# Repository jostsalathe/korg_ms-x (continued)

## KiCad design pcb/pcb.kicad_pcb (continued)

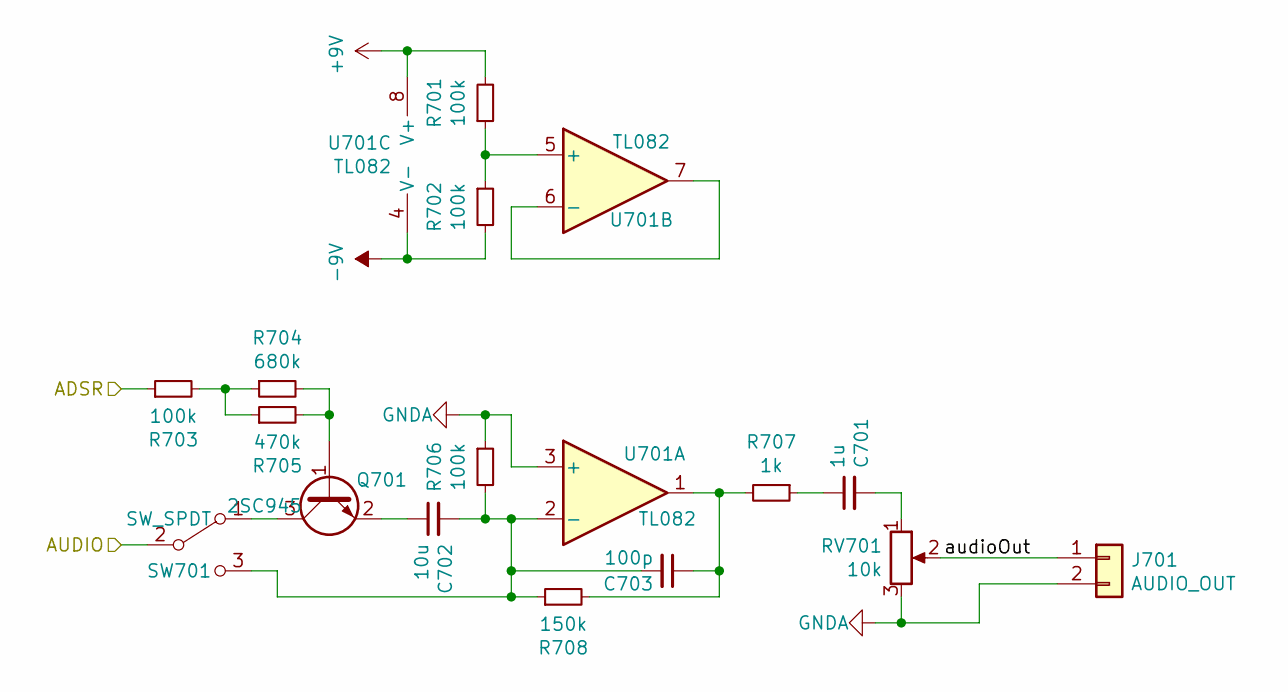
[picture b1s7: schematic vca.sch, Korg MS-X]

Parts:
C701: 1u; C_0805_2012Metric_Pad1.18x1.45mm_HandSolder; LCSC C28323
C702: 10u; C_0805_2012Metric_Pad1.18x1.45mm_HandSolder; LCSC C15850
C703: 100p; C_0805_2012Metric_Pad1.18x1.45mm_HandSolder; LCSC C1790
J701: AUDIO_OUT; PinHeader_1x02_P2.54mm_Vertical
Q701: 2SC945; SOT-23; LCSC C181154
R701, R702, R703, R706: 100k; R_0805_2012Metric_Pad1.20x1.40mm_HandSolder; LCSC C149504
R704: 680k; R_0805_2012Metric_Pad1.20x1.40mm_HandSolder; LCSC C17797
R705: 470k; R_0805_2012Metric_Pad1.20x1.40mm_HandSolder; LCSC C17709
R707: 1k; R_0805_2012Metric_Pad1.20x1.40mm_HandSolder; LCSC C17513
R708: 150k; R_0805_2012Metric_Pad1.20x1.40mm_HandSolder; LCSC C17470
RV701: 10k; PinHeader_1x03_P2.54mm_Vertical
SW701: SW_SPDT; PinHeader_1x03_P2.54mm_Vertical
U701: TL082; SOIC-8_3.9x4.9mm_P1.27mm; LCSC C9385

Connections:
+9V: R701.2, U701.8 (V+); also elsewhere on the board
-9V: R702.2, U701.4 (V-); also elsewhere on the board
/ADSR: R703.1; also elsewhere on the board
/AUDIO_RESONANCE: SW701.2 (B); also elsewhere on the board
/vca/audioOut: J701.1, RV701.2
GNDA: J701.2, R706.1, RV701.3, U701.3 (+); also elsewhere on the board
unnamed: C701.1, R707.1
unnamed: C701.2, RV701.1
unnamed: C702.1, Q701.2 (E)
unnamed: C702.2, C703.2, R706.2, R708.1, SW701.3 (C), U701.2 (-)
unnamed: C703.1, R707.2, R708.2, U701.1
unnamed: Q701.1 (B), R704.2, R705.2
unnamed: Q701.3 (C), SW701.1 (A)
unnamed: R701.1, R702.1, U701.5 (+)
unnamed: R703.2, R704.1, R705.1
unnamed: U701.6 (-), U701.7

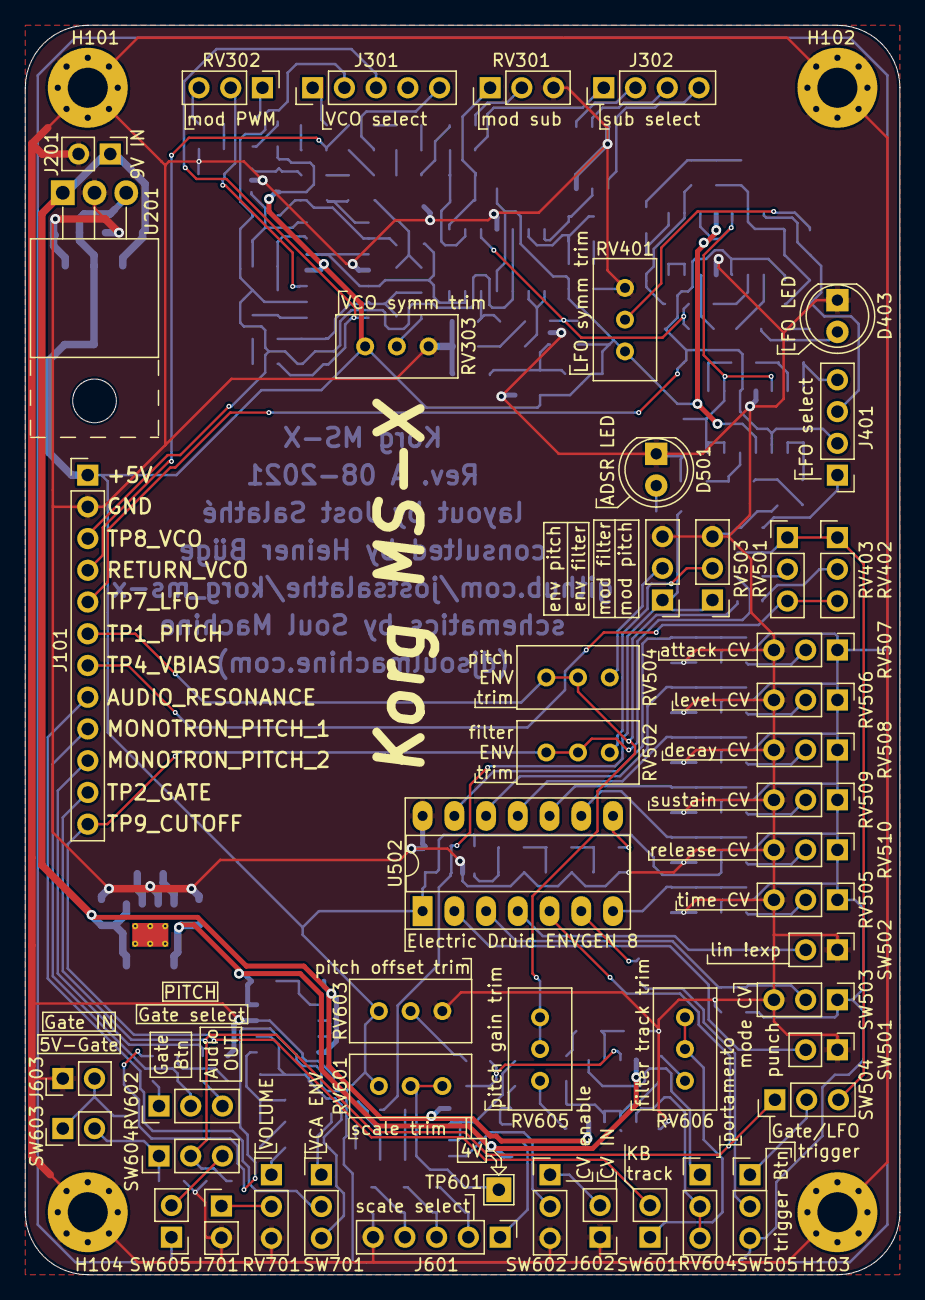
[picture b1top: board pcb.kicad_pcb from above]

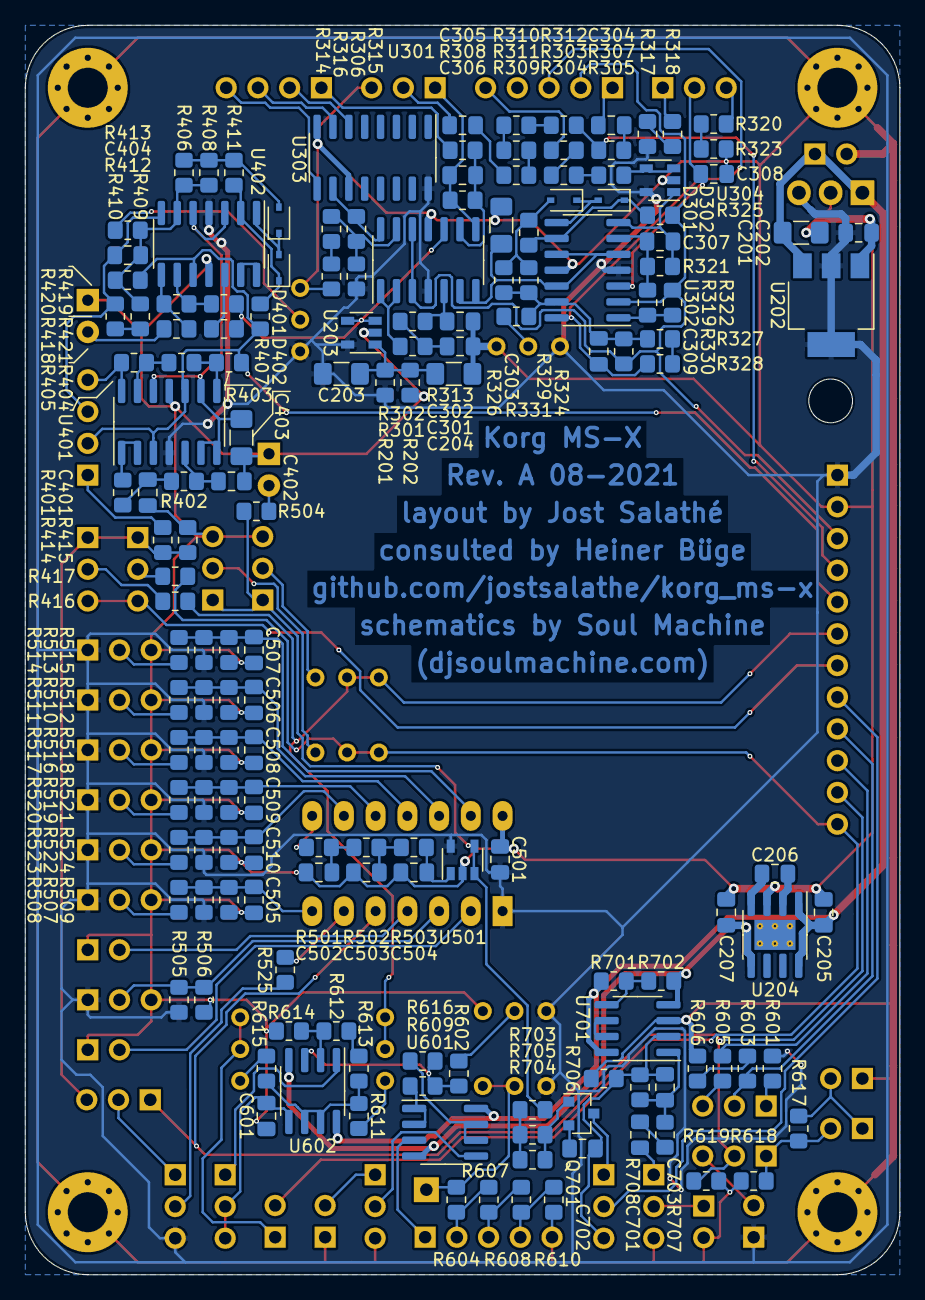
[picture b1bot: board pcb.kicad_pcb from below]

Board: 2 copper layers, 70.0 x 100.0 mm, 211 parts (159 on the bottom side), 143 nets.

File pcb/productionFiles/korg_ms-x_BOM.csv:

Comment,Designator,Footprint,LCSC Part Number
"100u","C201,C303,C403","Capacitor_SMD:C_1206_3216Metric_Pad1.42x1.75mm_HandSolder","C312983"
"10u","C202,C205,C206,C207,C308,C401,C402,C506,C601,C702","Capacitor_SMD:C_0805_2012Metric_Pad1.18x1.45mm_HandSolder","C15850"
"47u","C203,C204","Capacitor_SMD:C_1206_3216Metric_Pad1.42x1.75mm_HandSolder","C96123"
"1u","C301,C302,C304,C305,C701","Capacitor_SMD:C_0805_2012Metric_Pad1.18x1.45mm_HandSolder","C28323"
"100n","C306,C501,C505,C507,C508,C509,C510","Capacitor_SMD:C_0805_2012Metric_Pad1.18x1.45mm_HandSolder","C49678"
"470n","C307","Capacitor_SMD:C_0805_2012Metric_Pad1.18x1.45mm_HandSolder","C13967"
"22p","C309","Capacitor_SMD:C_0805_2012Metric_Pad1.18x1.45mm_HandSolder","C1804"
"500p","C404","Capacitor_SMD:C_0805_2012Metric_Pad1.18x1.45mm_HandSolder","C1747"
"47n","C502","Capacitor_SMD:C_0805_2012Metric_Pad1.18x1.45mm_HandSolder","C53134"
"4n7","C503","Capacitor_SMD:C_0805_2012Metric_Pad1.18x1.45mm_HandSolder","C1744"
"470p","C504","Capacitor_SMD:C_0805_2012Metric_Pad1.18x1.45mm_HandSolder","C1743"
"100p","C703","Capacitor_SMD:C_0805_2012Metric_Pad1.18x1.45mm_HandSolder","C1790"
"1N4148WS","D301,D302,D401,D402","Diode_SMD:D_SOD-323","C2128"
"LED","D403,D501","LED_THT:LED_D5.0mm",""
"MountingHole_Pad","H101,H102,H103,H104","MountingHole:MountingHole_3.2mm_M3_Pad_Via",""
"MONOTRON","J101","Connector_PinHeader_2.54mm:PinHeader_1x12_P2.54mm_Vertical",""
"PWR_IN","J201","Connector_PinHeader_2.54mm:PinHeader_1x02_P2.54mm_Vertical",""
"VCO_SEL","J301","Connector_PinHeader_2.54mm:PinHeader_1x05_P2.54mm_Vertical",""
"SUB_SEL","J302","Connector_PinHeader_2.54mm:PinHeader_1x04_P2.54mm_Vertical",""
"LFO_SEL","J401","Connector_PinHeader_2.54mm:PinHeader_1x04_P2.54mm_Vertical",""
"SCALE_SEL","J601","Connector_PinHeader_2.54mm:PinHeader_1x05_P2.54mm_Vertical",""
"CV_IN","J602","Connector_PinHeader_2.54mm:PinHeader_1x02_P2.54mm_Vertical",""
"GATE_IN","J603","Connector_PinHeader_2.54mm:PinHeader_1x02_P2.54mm_Vertical",""
"AUDIO_OUT","J701","Connector_PinHeader_2.54mm:PinHeader_1x02_P2.54mm_Vertical",""
"Net-Tie_2","NT201","NetTie:NetTie-2_SMD_Pad0.5mm",""
"2SC945","Q701","Package_TO_SOT_SMD:SOT-23","C181154"
"10k","R201,R202,R417,R501,R505,R506,R507,R509,R510,R512,R513,R515,R516,R518,R519,R521,R522,R524,R604,R607,R608,R610","Resistor_SMD:R_0805_2012Metric_Pad1.20x1.40mm_HandSolder","C17414"
"100k","R301,R302,R303,R304,R305,R307,R309,R310,R311,R312,R318,R324,R325,R326,R327,R328,R329,R330,R331,R401,R402,R404,R406,R407,R408,R409,R410,R411,R412,R413,R420,R421,R502,R602,R609,R612,R613,R614,R616,R701,R702,R703,R706","Resistor_SMD:R_0805_2012Metric_Pad1.20x1.40mm_HandSolder","C149504"
"33k","R306","Resistor_SMD:R_0805_2012Metric_Pad1.20x1.40mm_HandSolder","C17633"
"47","R308","Resistor_SMD:R_0805_2012Metric_Pad1.20x1.40mm_HandSolder","C17714"
"5k6","R313,R321","Resistor_SMD:R_0805_2012Metric_Pad1.20x1.40mm_HandSolder","C4382"
"4k7","R314","Resistor_SMD:R_0805_2012Metric_Pad1.20x1.40mm_HandSolder","C17673"
"1M","R315,R322,R403,R503","Resistor_SMD:R_0805_2012Metric_Pad1.20x1.40mm_HandSolder","C17514"
"47k","R316,R618","Resistor_SMD:R_0805_2012Metric_Pad1.20x1.40mm_HandSolder","C17713"
"56k","R317","Resistor_SMD:R_0805_2012Metric_Pad1.20x1.40mm_HandSolder","C17756"
"12","R319","Resistor_SMD:R_0805_2012Metric_Pad1.20x1.40mm_HandSolder","C204200"
"39k","R320,R419","Resistor_SMD:R_0805_2012Metric_Pad1.20x1.40mm_HandSolder","C25826"
"220k","R323","Resistor_SMD:R_0805_2012Metric_Pad1.20x1.40mm_HandSolder","C17556"
"22k","R405","Resistor_SMD:R_0805_2012Metric_Pad1.20x1.40mm_HandSolder","C17560"
"2k2","R414,R415,R416","Resistor_SMD:R_0805_2012Metric_Pad1.20x1.40mm_HandSolder","C17520"
"180","R418,R504","Resistor_SMD:R_0805_2012Metric_Pad1.20x1.40mm_HandSolder","C25270"
"1k","R508,R511,R514,R517,R520,R523,R525,R601,R605,R619,R707","Resistor_SMD:R_0805_2012Metric_Pad1.20x1.40mm_HandSolder","C17513"
"56","R603","Resistor_SMD:R_0805_2012Metric_Pad1.20x1.40mm_HandSolder","C17757"
"390","R606","Resistor_SMD:R_0805_2012Metric_Pad1.20x1.40mm_HandSolder","C17655"
"27k","R611","Resistor_SMD:R_0805_2012Metric_Pad1.20x1.40mm_HandSolder","C17593"
"330k","R615","Resistor_SMD:R_0805_2012Metric_Pad1.20x1.40mm_HandSolder","C17629"
"68k","R617","Resistor_SMD:R_0805_2012Metric_Pad1.20x1.40mm_HandSolder","C17801"
"680k","R704","Resistor_SMD:R_0805_2012Metric_Pad1.20x1.40mm_HandSolder","C17797"
"470k","R705","Resistor_SMD:R_0805_2012Metric_Pad1.20x1.40mm_HandSolder","C17709"
"150k","R708","Resistor_SMD:R_0805_2012Metric_Pad1.20x1.40mm_HandSolder","C17470"
"10k","RV301,RV501,RV503,RV505,RV506,RV507,RV508,RV509,RV510,RV602,RV701","Connector_PinHeader_2.54mm:PinHeader_1x03_P2.54mm_Vertical",""
"100k","RV302","Connector_PinHeader_2.54mm:PinHeader_1x03_P2.54mm_Vertical",""
"10k","RV303,RV401,RV601,RV603,RV605","Potentiometer_THT:Potentiometer_Bourns_3296W_Vertical",""
"20k","RV402,RV403","Connector_PinHeader_2.54mm:PinHeader_1x03_P2.54mm_Vertical",""
"100k","RV502,RV504,RV606","Potentiometer_THT:Potentiometer_Bourns_3296W_Vertical",""
"220k","RV604","Connector_PinHeader_2.54mm:PinHeader_1x03_P2.54mm_Vertical",""
"SW_SPST","SW501,SW502,SW601,SW603,SW605","Connector_PinHeader_2.54mm:PinHeader_1x02_P2.54mm_Vertical",""
"SW_SPDT_MSM","SW503","Connector_PinHeader_2.54mm:PinHeader_1x03_P2.54mm_Vertical",""
"SW_SPDT","SW504,SW602,SW604,SW701","Connector_PinHeader_2.54mm:PinHeader_1x03_P2.54mm_Vertical",""
"SW_Push_SPDT","SW505","Connector_PinHeader_2.54mm:PinHeader_1x03_P2.54mm_Vertical",""
"scale4V","TP601","TestPoint:TestPoint_THTPad_2.0x2.0mm_Drill1.0mm",""
"L7805","U201","Package_TO_SOT_THT:TO-220-3_Horizontal_TabUp",""
"AMS1117-5.0","U202","Package_TO_SOT_SMD:SOT-223-3_TabPin2","C6187"
"LM321","U203,U304,U501","Package_TO_SOT_SMD:SOT-23-5","C7972"
"ICL7660S","U204","Package_SO:SOIC-8-1EP_3.9x4.9mm_P1.27mm_EP2.41x3.3mm_ThermalVias","C7535"
"LM324","U301,U302,U401,U402","Package_SO:SOIC-14_3.9x8.7mm_P1.27mm","C71035"
"4040","U303","Package_SO:SOIC-16_3.9x9.9mm_P1.27mm","C725347"
"ENVGEN8","U502","Package_DIP:DIP-14_W7.62mm_Socket_LongPads",""
"TL082","U601,U602,U701","Package_SO:SOIC-8_3.9x4.9mm_P1.27mm","C9385"

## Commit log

2021-07-20 initialized KiCAD project
2021-07-21 Finished power supply schematics.
2021-07-21 Added some packages and the 2V5 reference voltage as well as first parts for the VCO.
2021-07-21 Added PDF of schematics
2021-07-26 Started table with part numbers
2021-07-27 Finished the VCO schematics. Some footprints still missing, though.
2021-07-28 Finished lfo schematics and rectified some errors
2021-07-28 forgot schematics PDF
2021-07-30 Added and finished ADSR circuitry.
2021-07-31 Added and finished CV/GATE circuitry.
2021-07-31 Forgot to plot current state of schematics, again... :facepalm:
2021-08-21 Finished all schematics.
2021-08-21 Completed most of the layout. ADSR and CV circuitry still in progress...
2021-08-21 Finished routing of signals. RTemaining tasks are marking the pcb and cleaning up the silk screen.
2021-08-23 Finished Rev.A layout.
2021-08-27 Listed all parts and added JLCPCB part numbers
2021-08-27 italic and bold probably is cooler
2021-08-27 Changed RV605 and RV606 positions.
2021-08-27 Added JLCPCB part numbers to symbols and generated production files.
2021-08-28 Added a selector for sub oscillator octave. Aaaaand added Heiner Büge as consultant to the back copper layer.
2021-08-29 Modified the 50 Ohm resistor to 47 Ohm due to availability. This should have no effect on the synthesis. Routed signals for sub oscillator selection.
2021-09-12 Added note about the optionality of the pull-up and -down resistors on the ADSR CV inputs.
